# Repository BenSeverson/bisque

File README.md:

<p align="center">
  <picture>
    <source media="(prefers-color-scheme: dark)" srcset="docs/logo-banner-dark.svg" />
    
  </picture>
</p>

<p align="center">

</p>

<p align="center">
  <a href="https://benseverson.github.io/bisque/"><b>▶ Try the live web UI demo</b></a> — interactive, no hardware required
</p>

## Features

**Temperature Control**
- PID controller with auto-tuning (Ziegler-Nichols relay method)
- 1-second control loop with time-proportional SSR output
- Thermocouple calibration offset

**Firing Profiles**
- Up to 20 custom profiles with 16 segments each (ramp rate, target temp, hold time)
- Orton cone firing (cones 022-13) with slow, medium, and fast heating speeds
- Delayed start

**Safety**
- Over-temperature protection (hardware max 1400 C, user-configurable limit)
- Thermocouple fault detection (open circuit, short to GND/VCC)
- Rate-of-rise monitoring (detects runaway >2x programmed rate)
- Not-rising detection (alerts if <10 C rise in 15 min)
- Emergency stop with immediate SSR cutoff

**Web Dashboard**
- Real-time temperature chart with profile overlay (React + Recharts)
- Profile builder with cone fire mode
- Firing history with CSV trace export and cost estimation
- Settings: calibration, safety limits, webhooks, API token

**iOS App**
- Full remote control (SwiftUI)
- Finds the kiln on your Wi-Fi automatically (Bonjour), no IP address to type
- Dynamic Island live activities during firing
- Local notifications for firing complete/error

**LCD Display**
- 4.0" TFT (480x320) with LVGL, adaptive single-screen dashboard (idle/active/paused/complete/error)
- 5-way nav switch (up/down/select/left/right), SELECT-driven modals for profile pick and firing control

**Connectivity**
- Wi-Fi with mDNS (`bisque.local`)
- REST API with optional bearer token auth
- WebSocket for real-time streaming
- Webhook notifications (firing complete/error)

## Screenshots

**Web Dashboard** (React)

**LCD Display** (LVGL on 4.0" TFT)

**iOS App** (SwiftUI)

## Hardware

The controller is a single board in [`hardware/kicad/`](hardware/kicad/) — a full KiCad project (schematic + routed **4-layer** board, 100 × 100 mm). Its GPIO map is [`docs/pin-assignments.md`](docs/pin-assignments.md).

It integrates the ESP32-S3-WROOM-1U module (external U.FL antenna), two MAX31856 thermocouple front-ends, two SSR drive channels behind a hardware watchdog, a current-transformer input read by the ESP32's ADC, a ULN2003 auxiliary output bank, three protected dry-contact inputs, USB-C flashing, and an alarm buzzer — with screw terminals for the field wiring and keyed connectors for the display and nav-switch looms. Gerbers, drill files, and an assembly BOM/CPL are committed and ready to upload to a board house.

See [`hardware/kicad/README.md`](hardware/kicad/README.md) for the full BOM, fabrication notes, and the regeneration workflow. GPIO assignments mirror the firmware's `Kconfig` defaults, so stock firmware runs unmodified.

[`hardware/enclosure/`](hardware/enclosure/README.md) documents a complete enclosure build around an off-the-shelf wall-mount steel box — layout, SSR thermal sizing, mains/SELV segregation, and a printable 1:1 drill template for the door.

> **Safety warning:** Kilns operate at dangerous temperatures and voltages. Ensure all high-voltage wiring is performed by a qualified electrician. Use appropriate safety equipment and never leave a firing kiln unattended.

## Getting Started

### Prerequisites

- [ESP-IDF v6.1.1](https://docs.espressif.com/projects/esp-idf/en/v6.1.1/esp32s3/get-started/)
- Node.js 18+
- [XcodeGen](https://github.com/yonaskolb/XcodeGen) (for iOS development)

### Dev Container (recommended)

The fastest way to a reproducible toolchain is the VS Code dev container — it
pins the exact ESP-IDF v6.1.1 image CI uses plus Node 24, the static-analysis
tools, and the Claude Code CLI. Open the repo in VS Code and run **Dev
Containers: Reopen in Container**. Everything below (firmware build, web UI,
`make ci`) then works in the container terminal; only flashing needs a bench.
See [docs/devcontainer.md](docs/devcontainer.md).

### Firmware

```bash
# Build web UI assets first
cd web_ui && npm install && npm run build && cd ..

# Gzip assets for SPIFFS
gzip -k -9 spiffs_data/www/assets/*.js spiffs_data/www/assets/*.css

# Build and flash firmware
source ~/.espressif/v6.1.1/esp-idf/export.sh
idf.py build
idf.py flash monitor
```

### Web UI Development

```bash
cd web_ui
npm install
npm run dev    # Starts dev server with mock kiln simulator
```

### iOS App

```bash
# Generate Xcode project
cd ios/Bisque
xcodegen generate
open Bisque.xcodeproj
```

For simulator testing, start the mock server first:

```bash
cd web_ui && npm run mock-server   # HTTP + WebSocket on localhost:8080
```

In the iOS simulator, tap "Use Mock Server" on the connection screen.

<details>
<summary><strong>Simulator / Mock Server</strong></summary>

A mock kiln server simulates the full API (status, profiles, firing, settings, history, autotune, diagnostics) with realistic temperature physics so you can develop and test without hardware.

### Web UI development

The mock server runs automatically as a Vite plugin when you start the web UI dev server:

```bash
cd web_ui
npm run dev
```

The mock is enabled by default. To disable it and proxy to a real kiln instead:

```bash
VITE_MOCK=false npm run dev
```

Control simulation speed with `VITE_MOCK_SPEED` (default `60` = 60x real-time):

```bash
VITE_MOCK_SPEED=120 npm run dev
```

### iOS app development

A standalone mock server is available for testing the iOS app in the Xcode simulator:

```bash
cd web_ui
npm run mock-server
```

This starts an HTTP + WebSocket server on `localhost:8080`. To change the port or simulation speed:

```bash
MOCK_PORT=9000 MOCK_SPEED=120 npm run mock-server
```

### LCD Simulator

A standalone SDL2-based simulator renders the LVGL display UI on your desktop:

```bash
cd simulator
cmake -B build && cmake --build build
./build/bisque_sim
```

Requires SDL2 (`brew install sdl2` on macOS).

</details>

## Architecture

```
main/                 App entry point, FreeRTOS task creation
components/
  app_config/         Pin definitions, hardware constants
  thermocouple/       MAX31856 SPI driver (2 channels)
  pid_control/        PID controller + Ziegler-Nichols auto-tune
  firing_engine/      Multi-segment firing state machine
  safety/             Watchdog, over-temp, fault detection
  cone_table/         Orton cone temperature lookup (022-13)
  history/            Firing history + temperature traces (NVS)
  display/            ST7796S LCD + LVGL UI (adaptive dashboard)
  web_server/         REST API + WebSocket server
  wifi_manager/       Wi-Fi STA/AP + mDNS
web_ui/               React/TypeScript web dashboard
ios/Bisque/           SwiftUI iOS app
simulator/            LVGL SDL2 desktop simulator
tests/host/           Pure-logic + accelerated firing unit tests (CMake/Unity)
docs/                 Wiring diagrams, screenshots, bench smoke test
```

## Testing

CI runs five automated test layers on every PR — pure-logic unit tests
and accelerated firing scenarios (`tests/host/`), a UI screenshot
regression suite (`simulator/ --diff`), web UI unit tests, and a
cross-language API contract test that validates firmware JSON output
against the frontend's zod schemas.

Before tagging a release, run the [bench smoke test](docs/bench-smoke-test.md) — a 3-8 minute hardware
run that verifies the parts CI can't touch: real SSR clicks, real
thermocouple readings, history persistence across reboot.

## Network security

**Bisque assumes the network it sits on is trusted.** It is a LAN-only
device: the HTTP API and the WebSocket telemetry feed are plain `http://`
and `ws://`, with no TLS. Anyone who can see traffic on the same Wi-Fi can
read the API token and every command sent with it.

The optional API token (Settings → API Token) is therefore a lock on the
front door, not protection against a hostile network. It stops a
housemate's laptop or a curious guest from starting a firing; it does not
stop someone who is already capturing your Wi-Fi traffic. Concretely:

- The token is sent as an `Authorization: Bearer` header on every REST
  request and compared in constant time on the device.
- The WebSocket telemetry feed (`/api/v1/ws`) is authenticated by the same
  check as the REST API. Browsers cannot set headers on a WebSocket
  handshake, so the web UI presents the token as a `?token=` query
  parameter instead — which means that on this one route the credential does
  reach anywhere the URL does, including proxy logs and browser history. The
  iOS app uses `URLSession`, which can set the header, and does. Dropping the
  query parameter would lock every browser out of live telemetry, so it is a
  deliberate trade rather than an oversight.
- Firmware updates are fetched over HTTPS with certificate validation
  against the bundled root store, and the downloaded image is checked
  against the SHA-256 in the release manifest. So an OTA is not exposed by
  the local network being readable — its trust rests on GitHub's TLS, not on
  your LAN.

If that trust assumption does not hold for your network, put the kiln on an
isolated VLAN or guest SSID rather than relying on the token. TLS on-device
with certificate pinning in the clients has been considered and is tracked
in [#149](https://github.com/BenSeverson/bisque/issues/149); it is a
significant amount of firmware and app complexity for a home LAN, and has
not been implemented.

**Never expose a kiln controller directly to the internet.** No port
forwarding, no DMZ. This is a device that applies mains power to a heating
element in an unattended room.

## Releases

Firmware is distributed as [GitHub Releases](https://github.com/BenSeverson/bisque/releases),
each with a full ESP32-S3 flash kit and Sigstore build-provenance
attestations. See [RELEASING.md](RELEASING.md) for the versioning scheme and
the procedure for cutting a release.

## License

[MIT](LICENSE)

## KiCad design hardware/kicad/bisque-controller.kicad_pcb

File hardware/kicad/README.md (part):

# Bisque Kiln Controller — KiCad PCB

The controller board. This is **rev B**, a respin of the original prototype
rather than a variant — it replaced the thermocouple front-end with an
incompatible part, added a second SSR zone and a digital current-sense chip,
moved most GPIOs, and swapped the module variant.
4-layer, 100 × 100 mm, built for **JLCPCB assembly**: 0805 passives,
QFN/TSSOP/SOIC/SOT ICs, SMD tact switches and the ESP32-S3-WROOM-1U module's
castellated pads all go down the SMT line, and JLCPCB hand-solders the fourteen
through-hole parts (terminals, wafers, buzzer) on the same order — see
"Fabrication & assembly" below for why that is cheaper than fitting them
yourself. The design record for
this respin, including the routing escalation that forced the layer count,
is `docs/superpowers/specs/2026-08-10-pcb-rev-b-hardware-design.md`; the
fab-readiness sign-off is `FAB-READINESS-REVIEW-REVB.md`.

**Rev C (2026-11-26)** is the current revision. It removes two blocks from
B.5 and changes the pin map for the first time since rev B: the WS2812 status
LED is gone (its indications live on the LCD and the web UI), and the ADE7953
metering chip, its oscillator and the second CT terminal are replaced by one
current-transformer input read by the ESP32's own ADC. 31 parts out, 6 in, 167
placed, 49 BOM lines. The reasoning is the rev C section of `DESIGN-NOTES.md`.
Much of this README is a record of how the board got here, so U7, Y1, LED1 and
J17 still appear below wherever the story involves them; the sections that
describe the board as it is (features, bill of materials, fabrication) are
current.

Built and validated with **real KiCad** (10.0.5, pcbnew Python API +
kicad-cli): footprints come from KiCad's installed libraries, ground/power
plane pours are filled and checked by `kicad-cli pcb drc --refill-zones` —
**zero errors, zero unconnected, zero warnings**
(`bisque-controller-drc.rpt`) — and the schematic passes a netlist round-trip
check (KiCad's exported netlist diffed against the design's connectivity
table — 92 nets, 0 mismatches). The 3D renders in `3d/` are raytraced by
`kicad-cli pcb render` with the official component models.

| File | What it is |
|---|---|
| `bisque-controller.kicad_pro` | Project. Hand-maintained **except** two blocks, both derived and both written *after* the board is saved because `pcbnew.SaveBoard()` blanks them: `schematic.top_level_sheets` (`project_sync.py::sync_project()`) and `net_settings` (`gen_pcb.py::sync_netclasses()`, from `ROUTE_ORDER`) — see below |
| `bisque-controller.kicad_sch` | Root of the hierarchical schematic: a sheet symbol per functional area (`sheets/power`, `mcu`, `kiln`, `io`, `ct`) plus the notes block and the mechanical parts (mounting holes H1–H4, fiducials FID1–FID3), wired as a block diagram: each sheet symbol carries a pin per net that crosses sheets. Within a sheet: one hierarchical label per crossing net, local labels for everything else, real power ports for rails; no global labels. Hand-owned; `make pcb-netlist` exports its connectivity. |
| `bisque-controller.kicad_pcb` | Board: placed, fully routed, 4 layers (F.Cu/B.Cu signals, In1.Cu GND plane, In2.Cu +3V3 plane), on JLCPCB's `JLC04161H-7628` 1.6 mm stack-up — see "The physical stack-up" |
| `bisque-controller.kicad_dru` | JLCPCB's standard 4-layer process as KiCad custom rules — **not generated**, and not a statement of design intent: every limit in it is JLC's *absolute minimum*, so a violation means something slipped off the design's own floor (0.3 mm track, 0.2 mm clearance, 0.6/0.3 vias, all from `net_settings`) far enough to hit the fab's. KiCad reads it by project name, so it survives regeneration untouched and the existing `kicad-cli pcb drc` pass picks it up for free — see "Fabrication & assembly at JLCPCB" |
| `3d/board-3d-*.png` | Raytraced renders, kicad-cli — straight orthographic **top** and **bottom** only. The angled iso/front views were dropped: they look better than they read, and these images get used to check placement and silk, not to advertise |
| `bisque-controller-drc.rpt` | KiCad DRC report, now including the `.kicad_dru` rules above (0 errors, 0 unconnected, 0 warnings — the 109 silkscreen warnings went with the silk packer, see "Regenerating the files") |
| `gerbers/` | Fabrication outputs (kicad-cli: F.Cu, B.Cu, **In1.Cu, In2.Cu**, paste/silk/mask, Edge.Cuts, Excellon drill + job file) |
| `pdf/` | Schematic and board PDFs (kicad-cli) |
| `jlcpcb/` | The complete JLCPCB upload: `gerbers.zip` for fabrication, BOM + CPL for assembly, plus the shopping list for the parts you could hand-solder instead, and `mouser-order.csv` for the mating connectors |
| `generator/` | Scripts that build everything from one connectivity table |

## Opening it

Open `bisque-controller.kicad_pro` in KiCad 10 or newer (the board file
format and pcbnew API this generator uses require it — see "Regenerating the
files"). Zones ship **filled** (KiCad's own filler) and the board already
passes KiCad DRC; re-run it after any edit. The schematic embeds its
symbols; the board references the standard KiCad footprint libraries (and
was generated from them), plus the four vendored models in `3dmodels/`.

**Opening the project used to dirty it.** KiCad records the root sheet under
`schematic.top_level_sheets` in the `.kicad_pro` and writes that block itself
the first time anything touches the project — and what it writes depends on
who wrote it. The GUI knows the schematic's real root uuid; `kicad-cli pcb`
fills all-zeros, because the PCB tooling never loads a schematic and has no
uuid to record. So the file grew an unexplained diff after a regen and could
flip between two values depending on which tool ran last.

`project_sync.py::sync_project()` (used by `sync_board.py`) now derives the entry from the same `ROOT`
constant the schematic's own `(uuid ...)` comes from, and runs on every
`pcb-sync`. Whoever opens the project next finds it already
correct and leaves it alone — kicad-cli only ever *adds* the block when it is
missing and preserves a populated one, which is what makes deriving it
sufficient rather than a tug-of-war. The rewrite is a whole-file json
round-trip, safe because KiCad emits plain 2-space-indented JSON that
re-dumps byte for byte; do not replace it with a hand-rolled text patch.

## What's on the board

- **U1 — ESP32-S3-WROOM-1U-N16R2** module (16 MB flash / 2 MB **quad**
  PSRAM — matches `sdkconfig.defaults`' `CONFIG_SPIRAM_MODE_QUAD` + the
  16 MB OTA partition table), at the top edge. The **1U** variant carries a
  **U.FL connector for an external antenna** rather than the standard
  WROOM-1's on-package PCB antenna: a kiln controller mounts on or near a
  large grounded steel enclosure, which makes a PCB antenna close to
  non-functional, and the 1U's antenna can be placed on a pigtail somewhere
  that actually radiates. It also reclaims the ~330 mm² antenna keep-out
  band the WROOM-1 footprint would require — freed for parts and ground
  pour on a board that turned out to need every square millimeter (see
  "Density and the 4-layer stack-up" below). **The U.FL pigtail (U.FL → SMA
  bulkhead) and the 2.4 GHz antenna are accessories, not BOM lines** — buy
  them separately (see the hand-solder/shopping-list note below) and drill
  an SMA bulkhead hole in the enclosure. U.FL is rated for ~30 mating
  cycles, so treat the connection as assemble-once, not a field-serviceable
  connector.

  **Certification caveat.** Espressif's modular certification for the
  WROOM-1U is granted against specific antenna types and gains. Fitting a
  non-approved (e.g. high-gain) antenna steps outside that approval — see
  `CERT-001` in `FAB-READINESS-REVIEW-REVB.md`. Use an antenna within the
  certified list unless you're prepared to re-certify.

- **Power**: 24 V DC in on screw terminal **J2** (top-left) *or* USB-C.
  The 24 V side runs J2 → F1 (750 mA/33 V resettable fuse) → D8 (SMAJ30A TVS)
  → **Q8** (AO3401A P-FET, reverse polarity) → **U11**, an XL1509-5.0 buck in
  the south-east corner that makes `BUCK_5V`; **U12** (TPS2116) then selects
  between `BUCK_5V` and USB VBUS to make `+5V`, and a **TLV1117LV33**
  (U2, SOT-223) drops that to 3V3.
  Regulating rather than dropping is the point: +5V used to be literally the
  input minus a Schottky, so every diode drop and every turn of the
  installer's trim pot landed on the SSR drive and the relay coil at once. Both of the board's remaining series diodes are now
  gone with it — the reverse-polarity SS34 is Q8 (~39 mV instead of ~0.4 V,
  which matters because `VIN_P` feeds both 24 V SSR terminals as well as the
  buck) and the USB ORing SS34 is U12 (~40 mΩ).

  **U12 runs in priority mode, not highest-voltage-wins, and that is the
  whole reason it is a mux and not an ideal diode.** A 5.25 V USB host is
  higher than a 5.0 V buck, so a plain ORing part would let a laptop source
  the relay bank and both SSR terminals; the diode used to prevent that for
  free by dropping. MODE ties to VIN1 and R63/R64 divide `BUCK_5V` into PR1
  with a 4.0 V threshold, so the buck wins whenever it is up. U12 also
  blocks USB back-feeding the unpowered buck, which closes fab-review
  finding **C1** (5 V on U11's FB and switch pins during every USB-only
  flashing session). Its ST pin is left unconnected on purpose — see
  `DESIGN-NOTES.md` at U12 for why that GPIO is not worth the route.

  `BUCK_5V` and `+5V` are deliberately separate nets: C44/**C46** are the
  buck's compensation (C46 is the electrolytic supplying the ESR zero — since
  2026-10-28 a Panasonic FK with its 0.36 Ω *specified* at 100 kHz, beside one
  22 µF ceramic rather than two; `DESIGN-NOTES.md` at C46 and C44) and
  belong on the buck's side of the mux, not the load's. The input pair C41/C42
  is chosen on Samsung's bias curve: 1210 X7R 4.7 µF holding 3.1 µF each at
  24 V, where the 1206 10 µF they replace held 1.35 µF. The 5 V rail is rated
  1.0 A at 50 °C in-box ambient (`DESIGN-NOTES.md` at C41, "LOAD BUDGET");
  the regulator's 2 A headline is not a rating of this board.
  Power LED (green) on 3V3. The display (below) draws from +5V directly, not
  through U2 — its backlight and panel logic were the dominant unmodeled load
  on the LDO, and moving them off keeps U2's junction temperature comfortably
  under its 125°C limit even at a hot enclosure ambient. The +3V3 rail also
  now lives on its own **inner plane** (In2.Cu) rather than a surface pour —
  see the stack-up note below.
- **Thermocouples ×2**: **MAX31856MUD+** (U3 channel 1 / U5 channel 2,
  TSSOP-14), K-type on screw terminals **J3** (channel 1) / **J8** (channel
  2), each with its datasheet-specified differential + common-mode input
  filter, sharing the SPI bus (MISO + its own CS: `TC1_CS` / `TC2_CS`). This
  replaces rev A's single MAX31855KASA+ entirely — the two parts are not
  pin-compatible, and no attempt was made to support both on one board.

  **Ungrounded-junction thermocouple probes are required.** Both MAX31856s
  reference their T− input to board ground. Two grounded-junction probes
  sharing one kiln chamber would form a ground loop through the kiln body
  itself; use ungrounded-junction (isolated-tip) K-type probes on both
  channels. This is a documentation obligation, not something the board
  enforces electrically.
- **SSR drive ×2, 24 V opto-driven high-side P-FET, ground-referenced (rev
  B.4)**: screw terminals **J4** (zone 1) / **J9** (zone 2), each
  **pin 1 = the switched +** (`SSR1_OUT` / `SSR2_OUT`, silk `OUT`) and
  **pin 2 = board `GND`**. Per channel: GPIO → 220 Ω → the LED of a TLP291
  (**U8** zone 1, **U9** zone 2) → GND; the opto's transistor pulls the gate
  of an **LP2309LT1G** (**Q5** / **Q6**, 60 V P-channel) down through
  **10 kΩ** (R69/R70), an **8.2 V zener** (D13/D14) gate-to-source sets the
  drive from the rail, and **10 kΩ** (R7/R20) gate-to-source holds it off.
  Both sources hang off **`SSR_24V`**, which is `VIN_P` through **Q9**, a
  third LP2309LT1G that is the watchdog's cutoff (see below). A green
  indicator LED (LED3/LED4, amber before the 2026-11-07 BOM-line merge) + 10 kΩ sits across each terminal pair, so it lights only
  when the channel is actually conducting. **D9**/**D10** freewheel each
  terminal for inductive loads. The board supplies the SSR control loop.
  (The SSRs themselves and all mains wiring stay outside this board.)
  Because the `−` pin is ground, an SSR lead that chafes onto the earthed
  enclosure is the wiring diagram, not a fault — the 2026-10-05 review's
  item 3, which B.2's switched-return topology could not cover. Rev B.2/B.3
  boards had pin 1 always live (silk `24V`) and switched the return; the
  pin order is unchanged, so a loom built to that silk still lands right.

  **Current budget, and it is a limit rather than a note.** The two channels
  share what is left of F1's *derated* hold current after the buck: **280 mA
  at the board's 50 °C in-box rating, 180 mA at 60 °C** (derived at F1 in
  `DESIGN-NOTES.md`, 2026-10-29, from the PPTC's derating table, the
  HDR-15-24's own derating and U11 at its 1.0 A ceiling). Two SSR inputs
  plus their indicators is ~40 mA and fits at any ambient. One 24 V coil
  beside an SSR: ≤ 260 mA (6.2 W) at 50 °C, ≤ 160 mA at 60 °C — a 5.4 W
  TeSys-D-class coil fits at 50 °C and not at 60. Two coils: ≤ 140 mA each
  at 50 °C, ≤ 90 mA each at 60 °C. The "~400 mA" quoted before was the 25 °C
  figure. F1 is not enlarged to buy more: under the in-box supply the
  supply's 0.63 A is the next limit anyway, and a 1.1 A PPTC's 2.2 A trip
  would put the clamped fault rail at 39.9 V against U11's 40 V.

  **The optocouplers are containment, not isolation, and that distinction is
  load-bearing.** Rev B opto-*isolated* both channels — dry-contact terminals,
  a four-layer pour keepout across the opto row, `SJ3`/`SJ4` to tie each
  collector to board +5 V, and `check_isolation.py` — and that was **reversed**
  before fab, because an optocoupler only isolates if the SSR control loop is
  powered from a supply that is *not this board*, and this board's is.
  **That reasoning still stands and is not being overturned.** These terminals
  are still board-powered, both sides still share `GND`, and there is still no
  pour keepout, no router keepout, no rule area and no `check_isolation.py`.
  Do not re-add any of them; read commit `93a31d7` first.

  What changed is the failure the parts are bought for. At 5 V, a channel
  MOSFET failing gate-to-drain put 5 V through 100 Ω into a GPIO and the
  ESP32's clamp survived it. At 24 V the same single failure puts ~240 mA into
  that clamp and takes the module with it. The opto removes the conductor: the
  only thing the MCU touches is an LED. It is also not more parts than the
  alternative — a gate-to-GND zener contains the same fault for the same one
  part per channel, but contains it *by conducting*, so it has to survive the
  fault to work and fails open silently.

  **The opto is a TLP291 in SOP-4, not the LTV-817S this started as, and the
  reason is geometry.** The SMD-DIP4 body is 12.04 mm across its courtyard;
  the corridor between `J4`/`J9` and the rest of the block is ~5.5 mm and has
  to carry both these parts and the four per-terminal legends (`OUT`/`GND`,
  each locked to its own screw's y and free only in x). A 12 mm opto leaves
  those legends nowhere to go, and they print on the terminal body — three
  `check_silk` failures that no amount of re-spacing fixes, because the
  corridor is simply too narrow. At 8.50 × 3.10 mm it opens to ~6.7 mm.
  It costs one Extended feeder where the LTV-817S was Basic, and buys 80 V
  `V_CEO` against 35 V, which is free margin on a 24 V board.

  The 220 Ω is sized against the ESP32's **guaranteed** `V_OH`
  (0.8 × VDD = 2.64 V), not against 3.3 V: the opto's CTR bin is only
  specified at `I_F` = 5 mA and falls off steeply below it, and 330 Ω at that
  corner gives 4.7 mA. 220 Ω gives 7.0 mA there, 5.6 mA with `V_F` also at
  its maximum, and 10.0 mA typical — half the ESP32's recommended source
  current.

  The gate drive comes from a **zener, not from the opto's CTR**, and that is
  deliberate: with the opto saturated the R69/R7 pair alone would put half
  the rail across the gate (11.9 V at 24 V, 18.8 V in a clamped 38 V fault,
  24 V on the 48 V transient), so D13/D14 clamp `V_SG` to 8.2 V from
  ~17 V upwards — the whole 21.6–29 V trim range and the fault alike. The
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
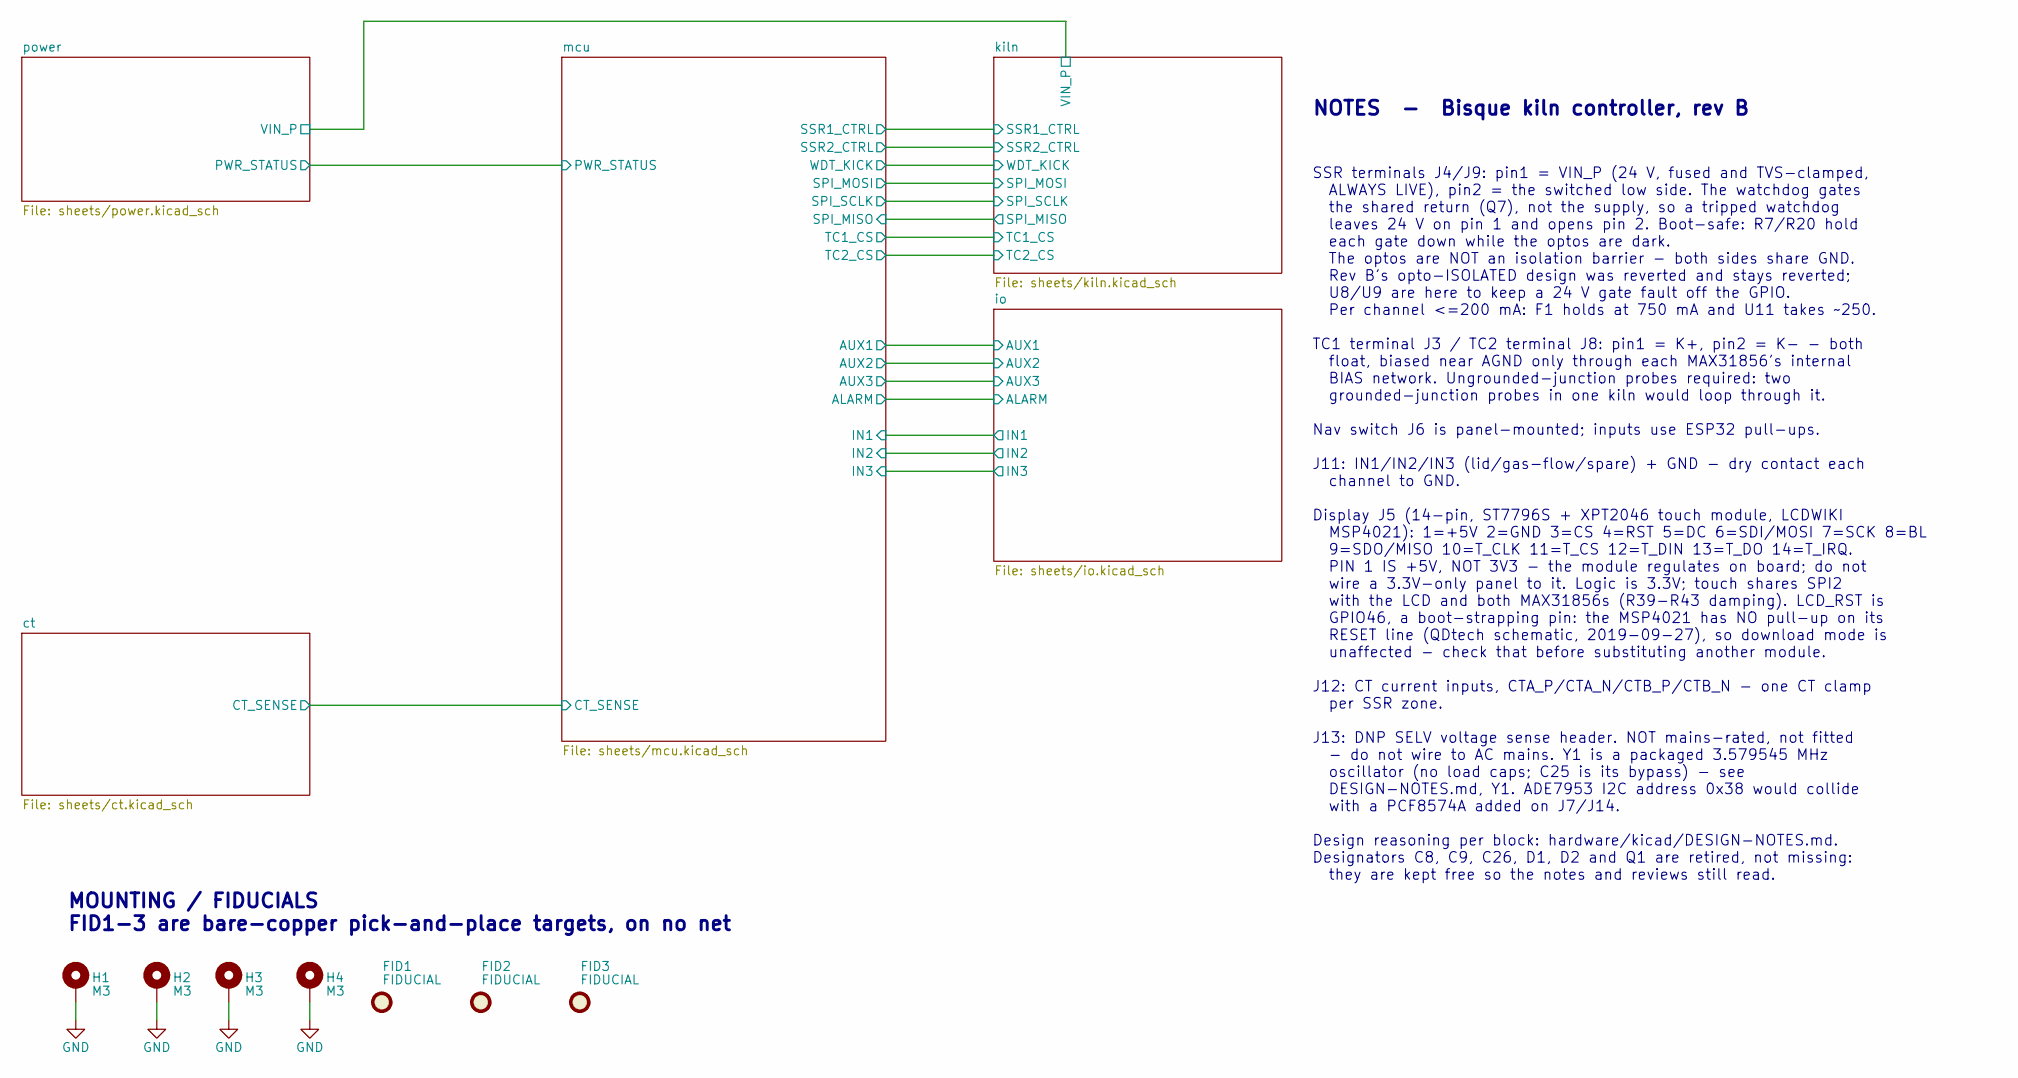
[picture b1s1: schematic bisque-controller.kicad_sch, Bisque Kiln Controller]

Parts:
FID1, FID2, FID3: FIDUCIAL; Fiducial_1mm_Mask2mm
H1, H2, H3, H4: M3; MountingHole_3.2mm_M3_Pad_Via

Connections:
GND: H1.1, H2.1, H3.1, H4.1; also elsewhere on the board

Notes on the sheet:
NOTES - Bisque kiln controller, rev B
SSR terminals J4/J9: pin1 = VIN_P (24 V, fused and TVS-clamped, ALWAYS LIVE), pin2 = the switched low side. The watchdog gates the shared return (Q7), not the supply, so a tripped watchdog leaves 24 V on pin 1 and opens pin 2. Boot-safe: R7/R20 hold each gate down while the optos are dark. The opto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
MOUNTING / FIDUCIALS FID1-3 are bare-copper pick-and-place targets, on no net

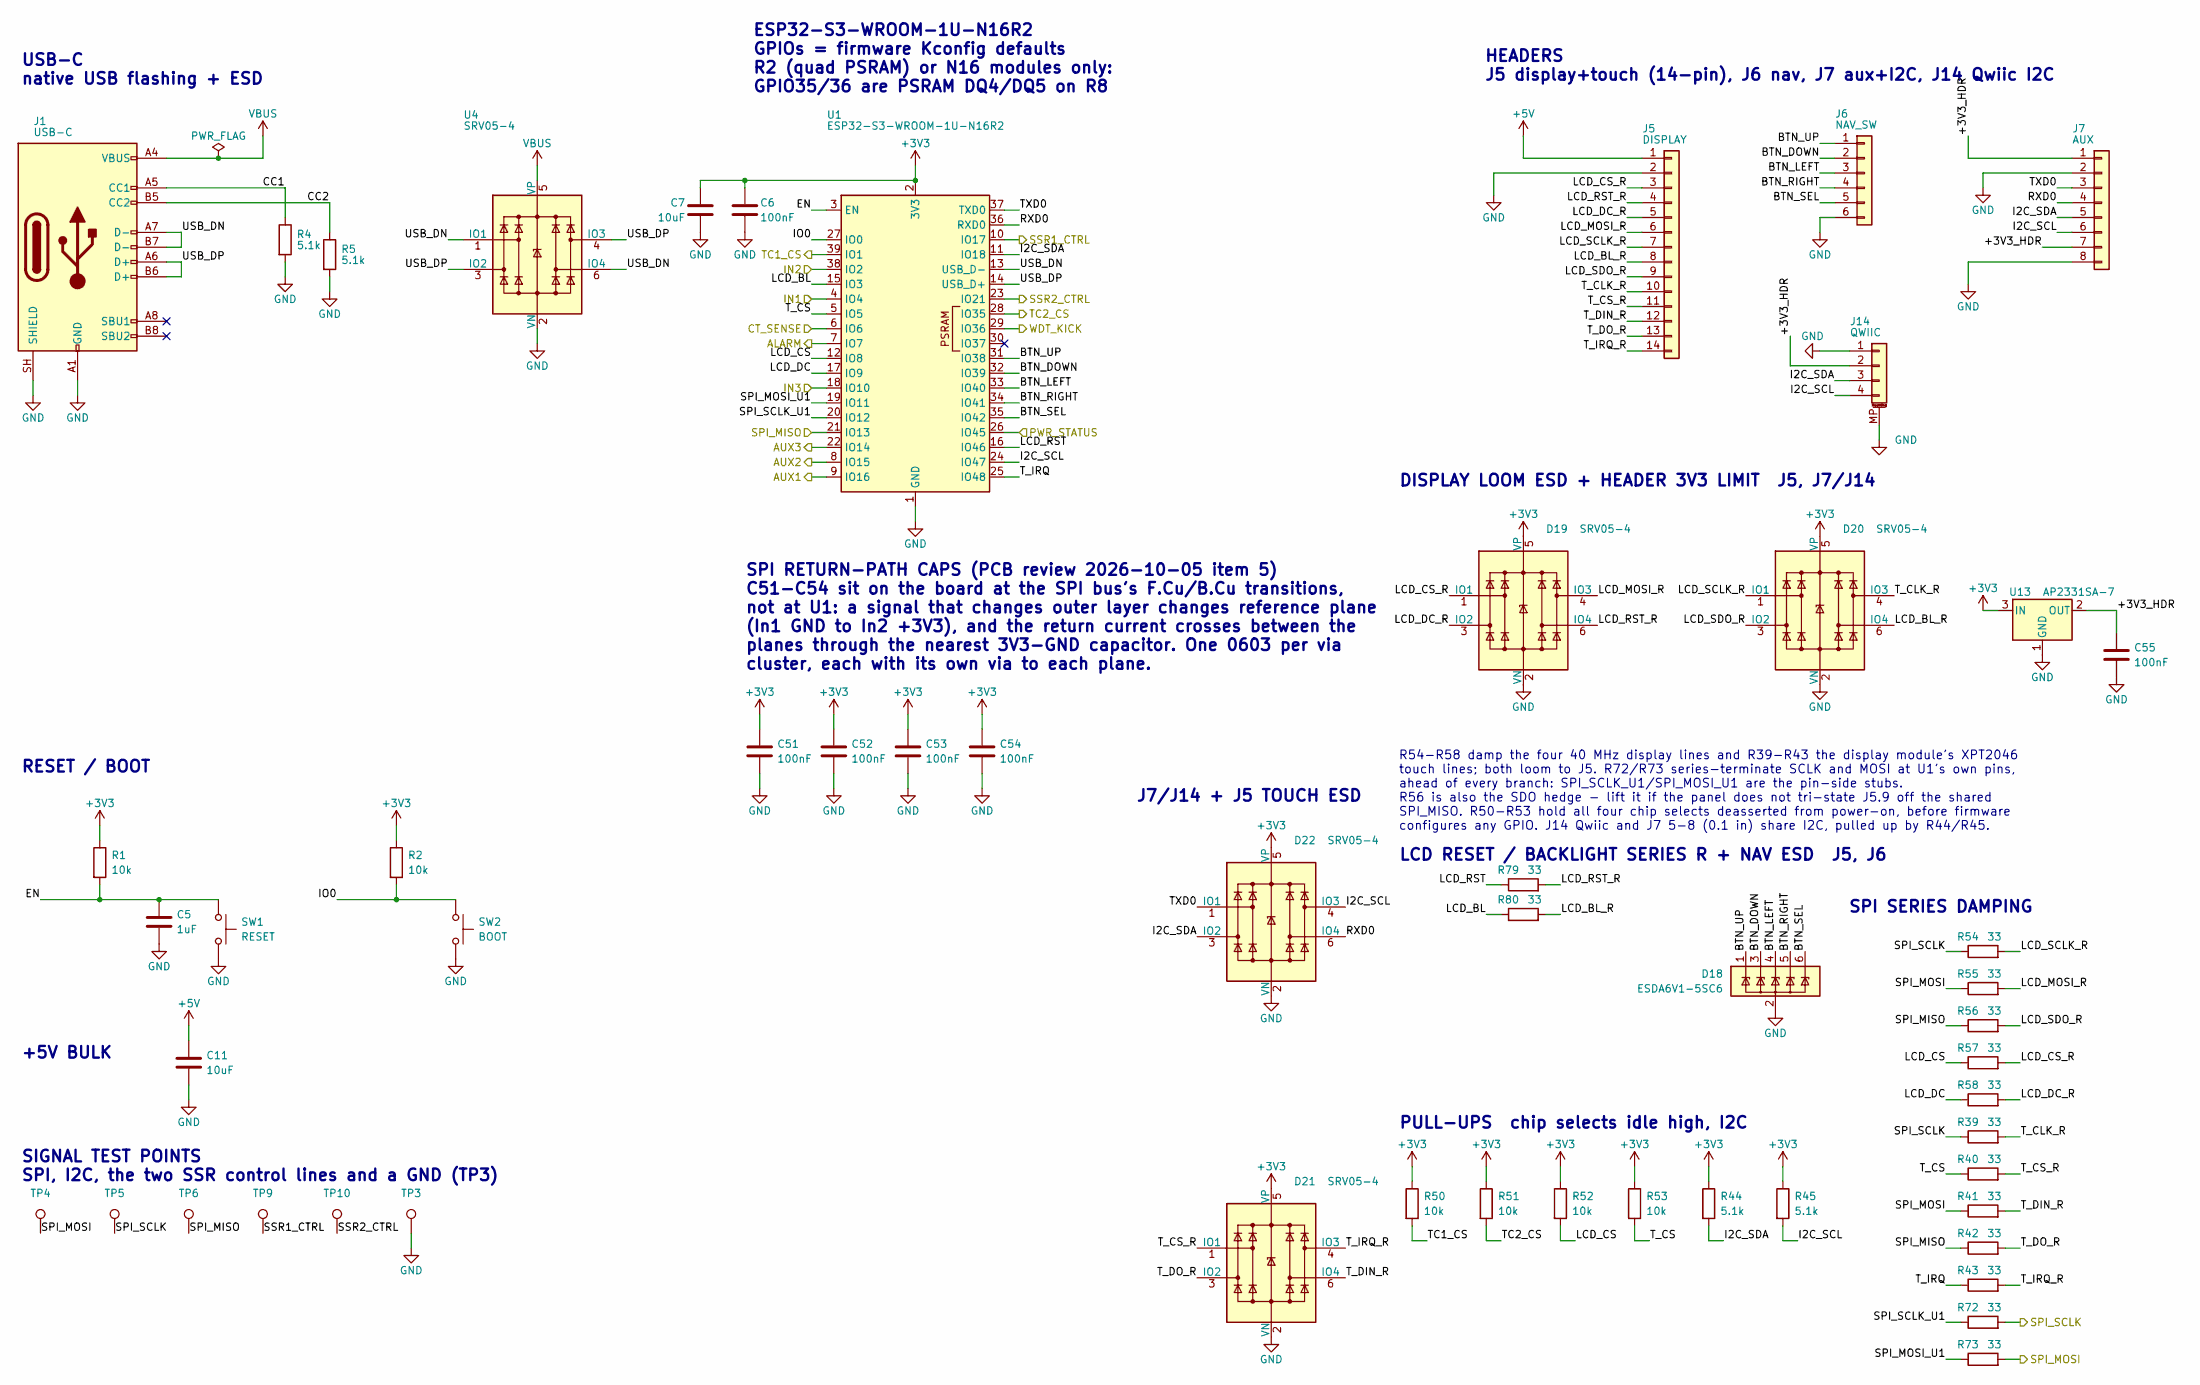
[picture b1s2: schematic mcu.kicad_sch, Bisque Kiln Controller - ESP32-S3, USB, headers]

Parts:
C5: 1uF; C_0805_2012Metric; MPN CL21B105KBFNNNE; LCSC C28323
C6, C51, C52, C53, C54, C55: 100nF; C_0603_1608Metric; MPN CC0603KRX7R9BB104; LCSC C14663
C7, C11: 10uF; C_0805_2012Metric; MPN CL21A106KAYNNNE; LCSC C15850
D18: ESDA6V1-5SC6; SOT-23-6; MPN ESDA6V1-5SC6; LCSC C2827672
D19, D20, D21, D22: SRV05-4; SOT-23-6; MPN SRV05-4; LCSC C7420376
J1: USB-C; USB_C_Receptacle_HRO_TYPE-C-31-M-12; MPN TYPE-C-31-M-12; LCSC C165948
J5: DISPLAY; Molex_KK-254_AE-6410-14A_1x14_P2.54mm_Vertical; MPN XD-2510-14A; LCSC C17701004
J6: NAV_SW; Molex_KK-254_AE-6410-06A_1x06_P2.54mm_Vertical; MPN A2547WV-6P; LCSC C239381
J7: AUX; Molex_KK-254_AE-6410-08A_1x08_P2.54mm_Vertical; MPN 22272081; LCSC C240822
J14: QWIIC; JST_SH_SM04B-SRSS-TB_1x04-1MP_P1.00mm_Horizontal; MPN SM04B-SRSS-TB(LF)(SN); LCSC C160404
R1, R2, R50, R51, R52, R53: 10k; R_0805_2012Metric; MPN 0805W8F1002T5E; LCSC C17414
R4, R5, R44, R45: 5.1k; R_0805_2012Metric; MPN 0805W8F5101T5E; LCSC C27834
R39, R40, R41, R42, R43, R54, R55, R56, R57, R58, R72, R73, R79, R80: 33; R_0603_1608Metric; MPN 0603WAF330JT5E; LCSC C23140
SW1: RESET; SW_Push_1P1T_XKB_TS-1187A; MPN TS-1187A-B-A-B; LCSC C318884
SW2: BOOT; SW_Push_1P1T_XKB_TS-1187A; MPN TS-1187A-B-A-B; LCSC C318884
TP3: GND; TestPoint_Pad_D1.0mm
TP4: SPI_MOSI; TestPoint_Pad_D1.0mm
TP5: SPI_SCLK; TestPoint_Pad_D1.0mm
TP6: SPI_MISO; TestPoint_Pad_D1.0mm
TP9: SSR1_CTRL; TestPoint_Pad_D1.0mm
TP10: SSR2_CTRL; TestPoint_Pad_D1.0mm
U1: ESP32-S3-WROOM-1U-N16R2; ESP32-S3-WROOM-1U; MPN ESP32-S3-WROOM-1U-N16R2; LCSC C3013945
U4: SRV05-4; SOT-23-6; MPN SRV05-4; LCSC C7420376
U13: AP2331SA-7; SOT-23; MPN AP2331SA-7; LCSC C500764

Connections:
+3V3: C6.1, C7.1, C51.1, C52.1, C53.1, C54.1, D19.5 (VP), D20.5 (VP), D21.5 (VP), D22.5 (VP), R1.1, R2.1, R44.1, R45.1, R50.1, R51.1, R52.1, R53.1, U1.2 (3V3), U13.3 (IN); also elsewhere on the board
+3V3_HDR: C55.1, J7.1, J7.7, J14.2, U13.2 (OUT)
+5V: C11.1, J5.1; also elsewhere on the board
ALARM: U1.7 (IO7); also elsewhere on the board
AUX1: U1.9 (IO16); also elsewhere on the board
AUX2: U1.8 (IO15); also elsewhere on the board
AUX3: U1.22 (IO14); also elsewhere on the board
BTN_DOWN: D18.3 (IO2), J6.2, U1.32 (IO39)
BTN_LEFT: D18.4 (IO3), J6.3, U1.33 (IO40)
BTN_RIGHT: D18.5 (IO4), J6.4, U1.34 (IO41)
BTN_SEL: D18.6 (IO5), J6.5, U1.35 (IO42)
BTN_UP: D18.1 (IO1), J6.1, U1.31 (IO38)
CC1: J1.A5 (CC1), R4.1
CC2: J1.B5 (CC2), R5.1
CT_SENSE: U1.6 (IO6); also elsewhere on the board
EN: C5.1, R1.2, SW1.1, U1.3 (EN)
GND: C5.2, C6.2, C7.2, C11.2, C51.2, C52.2, C53.2, C54.2, C55.2, D18.2 (GND), D19.2 (VN), D20.2 (VN), D21.2 (VN), D22.2 (VN), J1.A1 (GND), J1.A12 (GND), J1.B1 (GND), J1.B12 (GND), J1.SH (SHIELD), J5.2, J6.6, J7.2, J7.8, J14.1, J14.MP (MountPin), R4.2, R5.2, SW1.2, SW2.2, TP3.1, U1.1 (GND), U1.40 (GND), U1.41 (GND), U4.2 (VN), U13.1 (GND); also elsewhere on the board
I2C_SCL: D22.4 (IO3), J7.6, J14.4, R45.2, U1.24 (IO47)
I2C_SDA: D22.3 (IO2), J7.5, J14.3, R44.2, U1.11 (IO18)
IN1: U1.4 (IO4); also elsewhere on the board
IN2: U1.38 (IO2); also elsewhere on the board
IN3: U1.18 (IO10); also elsewhere on the board
IO0: R2.2, SW2.1, U1.27 (IO0)
LCD_BL: R80.1, U1.15 (IO3)
LCD_BL_R: D20.6 (IO4), J5.8, R80.2
LCD_CS: R52.2, R57.1, U1.12 (IO8)
LCD_CS_R: D19.1 (IO1), J5.3, R57.2
LCD_DC: R58.1, U1.17 (IO9)
LCD_DC_R: D19.3 (IO2), J5.5, R58.2
LCD_MOSI_R: D19.4 (IO3), J5.6, R55.2
LCD_RST: R79.1, U1.16 (IO46)
LCD_RST_R: D19.6 (IO4), J5.4, R79.2
LCD_SCLK_R: D20.1 (IO1), J5.7, R54.2
LCD_SDO_R: D20.3 (IO2), J5.9, R56.2
PWR_STATUS: U1.26 (IO45); also elsewhere on the board
RXD0: D22.6 (IO4), J7.4, U1.36 (RXD0)
SPI_MISO: R42.1, R56.1, TP6.1, U1.21 (IO13); also elsewhere on the board
SPI_MOSI: R41.1, R55.1, R73.2, TP4.1; also elsewhere on the board
SPI_MOSI_U1: R73.1, U1.19 (IO11)
SPI_SCLK: R39.1, R54.1, R72.2, TP5.1; also elsewhere on the board
SPI_SCLK_U1: R72.1, U1.20 (IO12)
SSR1_CTRL: TP9.1, U1.10 (IO17); also elsewhere on the board
SSR2_CTRL: TP10.1, U1.23 (IO21); also elsewhere on the board
TC1_CS: R50.2, U1.39 (IO1); also elsewhere on the board
TC2_CS: R51.2, U1.28 (IO35); also elsewhere on the board
TXD0: D22.1 (IO1), J7.3, U1.37 (TXD0)
T_CLK_R: D20.4 (IO3), J5.10, R39.2
T_CS: R40.1, R53.2, U1.5 (IO5)
T_CS_R: D21.1 (IO1), J5.11, R40.2
T_DIN_R: D21.6 (IO4), J5.12, R41.2
T_DO_R: D21.3 (IO2), J5.13, R42.2
T_IRQ: R43.1, U1.25 (IO48)
T_IRQ_R: D21.4 (IO3), J5.14, R43.2
USB_DN: J1.A7 (D-), J1.B7 (D-), U1.13 (USB_D-), U4.1 (IO1), U4.6 (IO4)
USB_DP: J1.A6 (D+), J1.B6 (D+), U1.14 (USB_D+), U4.3 (IO2), U4.4 (IO3)
VBUS: J1.A4 (VBUS), J1.A9 (VBUS), J1.B4 (VBUS), J1.B9 (VBUS), U4.5 (VP); also elsewhere on the board
WDT_KICK: U1.29 (IO36); also elsewhere on the board

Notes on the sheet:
USB-C native USB flashing + ESD
SPI RETURN-PATH CAPS (PCB review 2026-10-05 item 5) C51-C54 sit on the board at the SPI bus's F.Cu/B.Cu transitions, not at U1: a signal that changes outer layer changes reference plane (In1 GND to In2 +3V3), and the return current crosses between the planes through the nearest 3V3-GND capacitor. O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
RESET / BOOT
+5V BULK
R54-R58 damp the four 40 MHz display lines and R39-R43 the display module's XPT2046 touch lines; both loom to J5. R72/R73 series-terminate SCLK and MOSI at U1's own pins, ahead of every branch: SPI_SCLK_U1/SPI_MOSI_U1 are the pin-side stubs. R56 is also the SDO hedge - lift it if the panel does not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
PULL-UPS chip selects idle high, I2C
DISPLAY LOOM ESD + HEADER 3V3 LIMIT J5, J7/J14
J7/J14 + J5 TOUCH ESD
LCD RESET / BACKLIGHT SERIES R + NAV ESD J5, J6
SPI SERIES DAMPING
HEADERS J5 display+touch (14-pin), J6 nav, J7 aux+I2C, J14 Qwiic I2C
SIGNAL TEST POINTS SPI, I2C, the two SSR control lines and a GND (TP3)
ESP32-S3-WROOM-1U-N16R2 GPIOs = firmware Kconfig defaults R2 (quad PSRAM) or N16 modules only: GPIO35/36 are PSRAM DQ4/DQ5 on R8

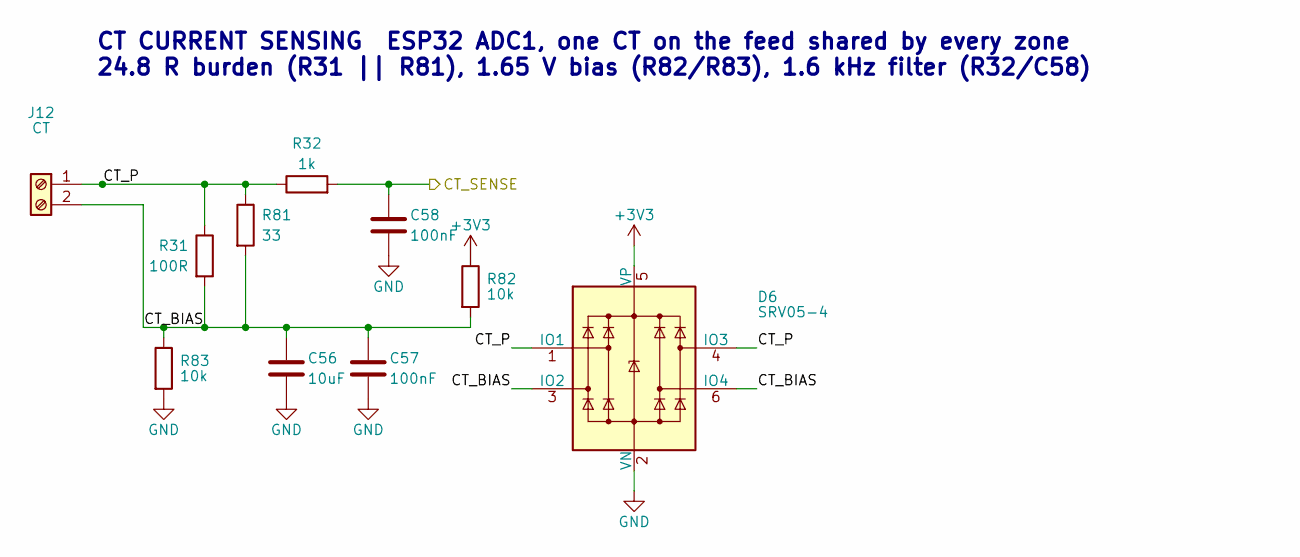
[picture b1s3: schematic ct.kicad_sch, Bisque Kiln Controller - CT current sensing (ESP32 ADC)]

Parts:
C56: 10uF; C_0805_2012Metric; MPN CL21A106KAYNNNE; LCSC C15850
C57, C58: 100nF; C_0603_1608Metric; MPN CC0603KRX7R9BB104; LCSC C14663
D6: SRV05-4; SOT-23-6; MPN SRV05-4; LCSC C7420376
J12: CT; TerminalBlock_Phoenix_MKDS-1,5-2-5.08_1x02_P5.08mm_Horizont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; MPN WJ500V-5.08-2P; LCSC C8465
R31: 100R; R_0805_2012Metric; MPN 0805W8F1000T5E; LCSC C17408
R32: 1k; R_0805_2012Metric; MPN 0805W8F1001T5E; LCSC C17513
R81: 33; R_0603_1608Metric; MPN 0603WAF330JT5E; LCSC C23140
R82, R83: 10k; R_0805_2012Metric; MPN 0805W8F1002T5E; LCSC C17414

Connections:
+3V3: D6.5 (VP), R82.1; also elsewhere on the board
CT_BIAS: C56.1, C57.1, D6.3 (IO2), D6.6 (IO4), J12.2, R31.2, R81.2, R82.2, R83.1
CT_P: D6.1 (IO1), D6.4 (IO3), J12.1, R31.1, R32.1, R81.1
CT_SENSE: C58.1, R32.2; also elsewhere on the board
GND: C56.2, C57.2, C58.2, D6.2 (VN), R83.2; also elsewhere on the board

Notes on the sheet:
CT CURRENT SENSING ESP32 ADC1, one CT on the feed shared by every zone 24.8 R burden (R31 || R81), 1.65 V bias (R82/R83), 1.6 kHz filter (R32/C58)

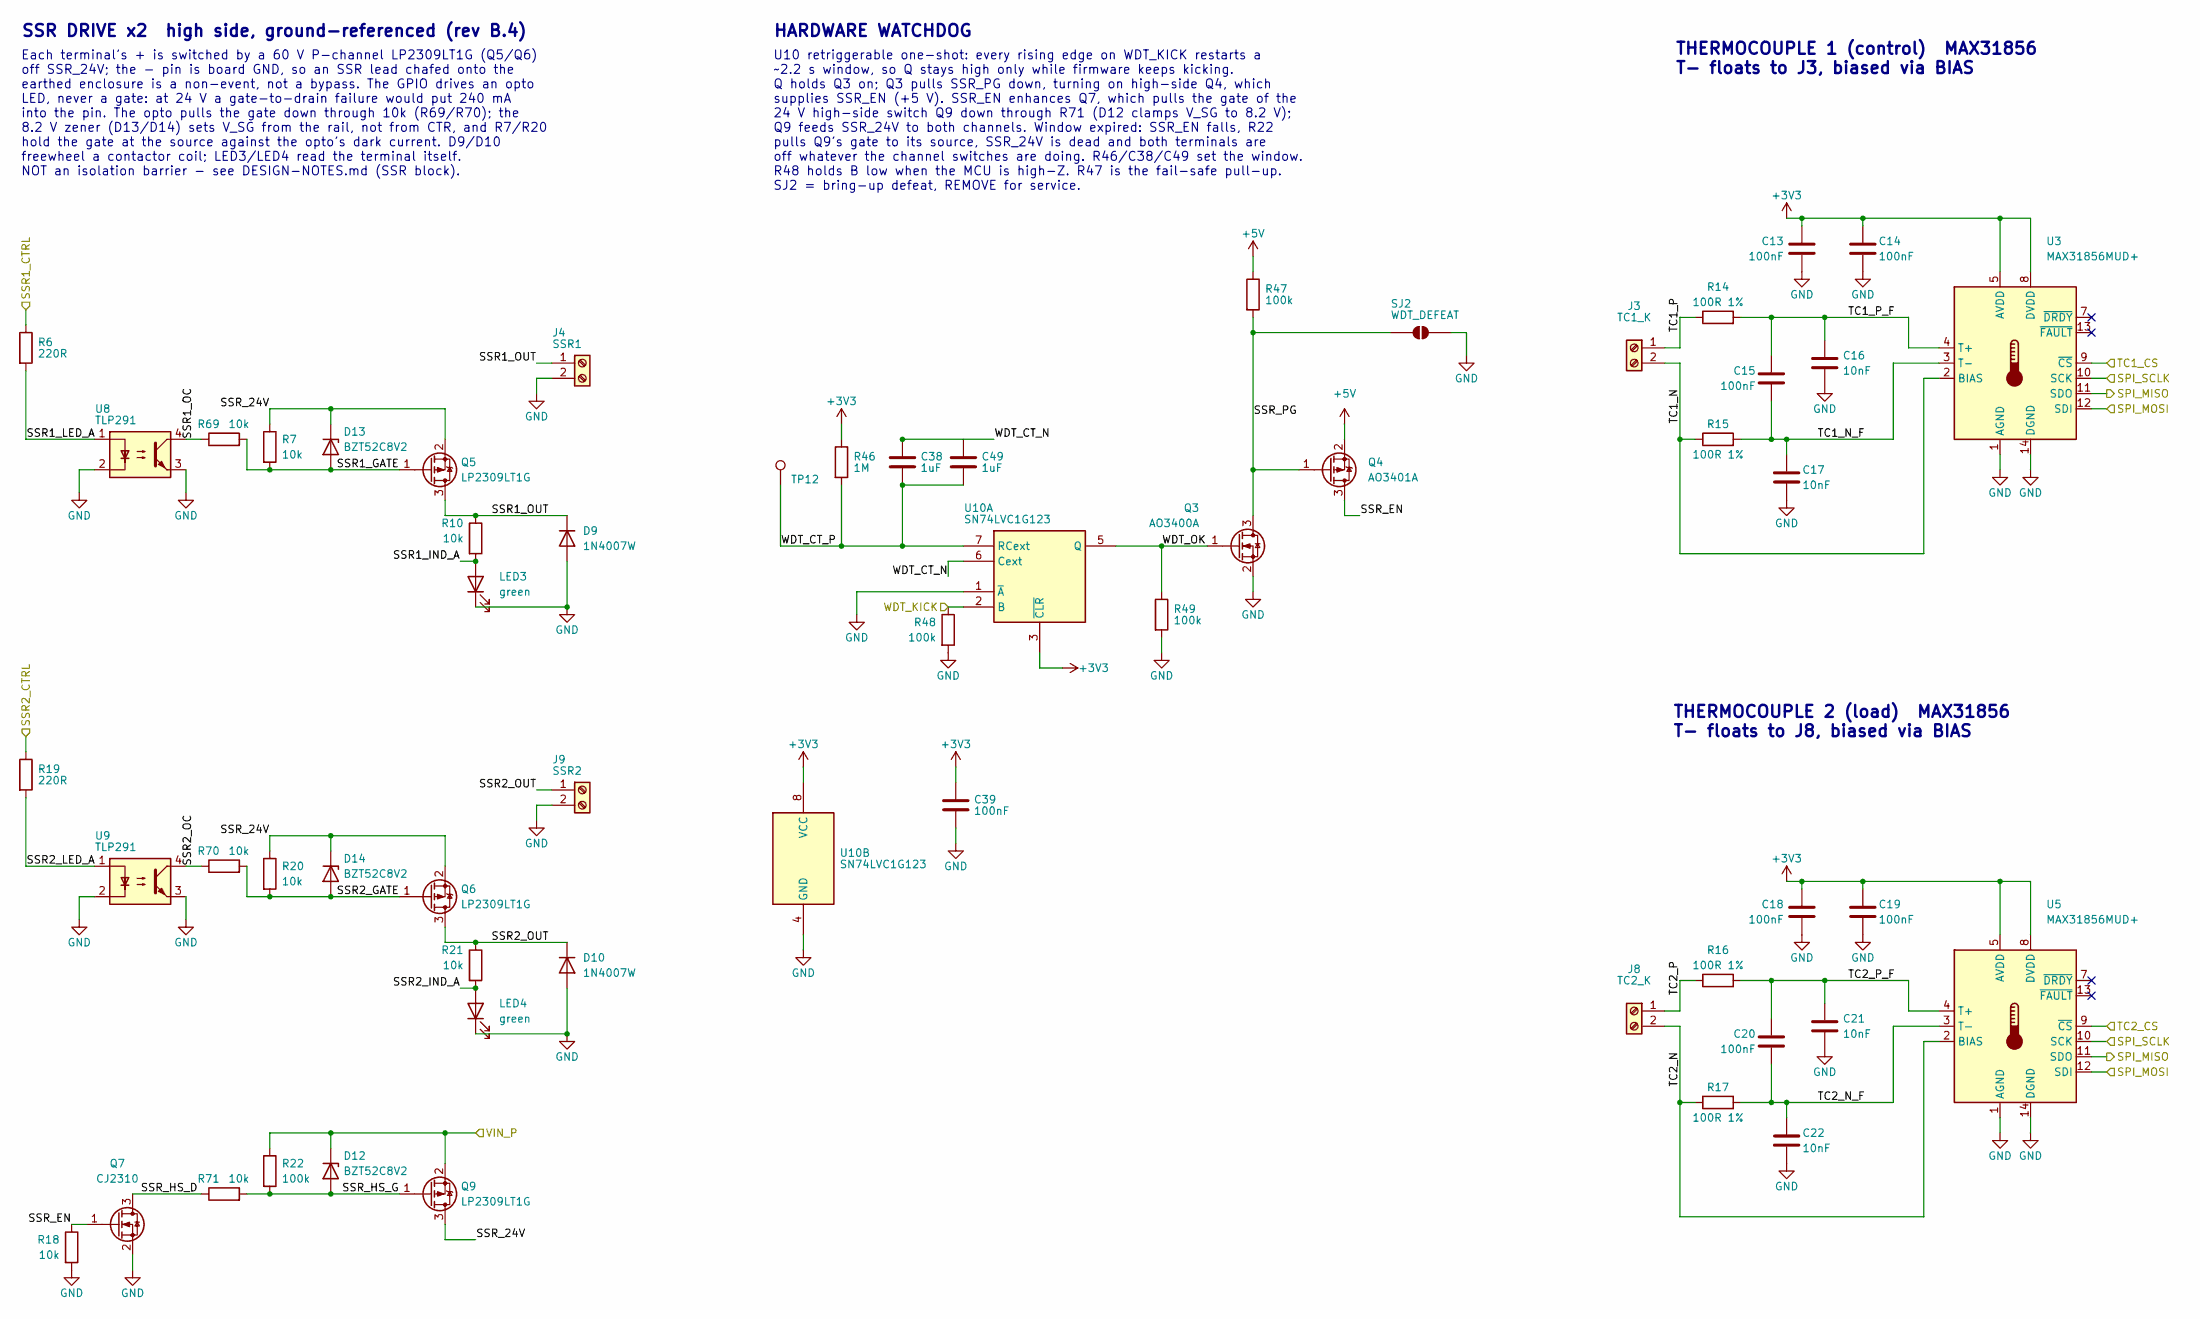
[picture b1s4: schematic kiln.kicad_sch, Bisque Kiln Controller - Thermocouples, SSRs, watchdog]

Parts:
C13, C14, C15, C18, C19, C20, C39: 100nF; C_0603_1608Metric; MPN CC0603KRX7R9BB104; LCSC C14663
C16, C17, C21, C22: 10nF; C_0805_2012Metric; MPN CL21B103KBANNNC; LCSC C1710
C38, C49: 1uF; C_0805_2012Metric; MPN CL21B105KBFNNNE; LCSC C28323
D9, D10: 1N4007W; D_SOD-123; MPN 1N4007W; LCSC C3018540
D12, D13, D14: BZT52C8V2; D_SOD-323; MPN BZT52C8V2S; LCSC C22375294
J3: TC1_K; TerminalBlock_Phoenix_MKDS-1,5-2-5.08_1x02_P5.08mm_Horizont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; MPN WJ500V-5.08-2P; LCSC C8465
J4: SSR1; TerminalBlock_Phoenix_MKDS-1,5-2-5.08_1x02_P5.08mm_Horizont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; MPN WJ500V-5.08-2P; LCSC C8465
J8: TC2_K; TerminalBlock_Phoenix_MKDS-1,5-2-5.08_1x02_P5.08mm_Horizont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; MPN WJ500V-5.08-2P; LCSC C8465
J9: SSR2; TerminalBlock_Phoenix_MKDS-1,5-2-5.08_1x02_P5.08mm_Horizont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; MPN WJ500V-5.08-2P; LCSC C8465
LED3, LED4: green; LED_0805_2012Metric; MPN KT-0805G; LCSC C2297
Q3: AO3400A; SOT-23; MPN AO3400A; LCSC C20917
Q4: AO3401A; SOT-23; MPN AO3401A; LCSC C15127
Q5, Q6, Q9: LP2309LT1G; SOT-23; MPN LP2309LT1G; LCSC C383253
Q7: CJ2310; SOT-23; MPN CJ2310; LCSC C75882
R6, R19: 220R; R_0805_2012Metric; MPN 0805W8F2200T5E; LCSC C17557
R7, R10, R18, R20, R21, R69, R70, R71: 10k; R_0805_2012Metric; MPN 0805W8F1002T5E; LCSC C17414
R14, R15, R16, R17: 100R 1%; R_0805_2012Metric; MPN 0805W8F1000T5E; LCSC C17408
R22, R47, R48, R49: 100k; R_0805_2012Metric; MPN 0805W8F1003T5E; LCSC C149504
R46: 1M; R_0805_2012Metric; MPN 0805W8F1004T5E; LCSC C17514
SJ2: WDT_DEFEAT; SolderJumper-2_P1.3mm_Open_RoundedPad1.0x1.5mm
TP12: WDT_CT_P; TestPoint_Pad_D1.0mm
U3, U5: MAX31856MUD+; TSSOP-14_4.4x5mm_P0.65mm; MPN MAX31856MUD+T; LCSC C2653162
U8, U9: TLP291; SOP-4_4.4x2.6mm_P1.27mm; MPN TLP291(GB-TP,SE; LCSC C55144
U10: SN74LVC1G123; SSOP-8_2.95x2.8mm_P0.65mm; MPN SN74LVC1G123DCTR; LCSC C123302

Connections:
+3V3: C13.1, C14.1, C18.1, C19.1, C39.1, R46.1, U3.5 (AVDD), U3.8 (DVDD), U5.5 (AVDD), U5.8 (DVDD), U10.3 (~CLR), U10.8 (VCC); also elsewhere on the board
+5V: Q4.2 (S), R47.1; also elsewhere on the board
GND: C13.2, C14.2, C16.2, C17.2, C18.2, C19.2, C21.2, C22.2, C39.2, D9.2 (A), D10.2 (A), J4.2, J9.2, LED3.1 (K), LED4.1 (K), Q3.2 (S), Q7.2 (S), R18.2, R48.2, R49.2, SJ2.2 (B), U3.1 (AGND), U3.14 (DGND), U5.1 (AGND), U5.14 (DGND), U8.2, U8.3, U9.2, U9.3, U10.1 (~A), U10.4 (GND); also elsewhere on the board
SPI_MISO: U3.11 (SDO), U5.11 (SDO); also elsewhere on the board
SPI_MOSI: U3.12 (SDI), U5.12 (SDI); also elsewhere on the board
SPI_SCLK: U3.10 (SCK), U5.10 (SCK); also elsewhere on the board
SSR1_CTRL: R6.1; also elsewhere on the board
SSR1_GATE: D13.2 (A), Q5.1 (G), R7.2, R69.2
SSR1_IND_A: LED3.2 (A), R10.2
SSR1_LED_A: R6.2, U8.1
SSR1_OC: R69.1, U8.4
SSR1_OUT: D9.1 (K), J4.1, Q5.3 (D), R10.1
SSR2_CTRL: R19.1; also elsewhere on the board
SSR2_GATE: D14.2 (A), Q6.1 (G), R20.2, R70.2
SSR2_IND_A: LED4.2 (A), R21.2
SSR2_LED_A: R19.2, U9.1
SSR2_OC: R70.1, U9.4
SSR2_OUT: D10.1 (K), J9.1, Q6.3 (D), R21.1
SSR_24V: D13.1 (K), D14.1 (K), Q5.2 (S), Q6.2 (S), Q9.3 (D), R7.1, R20.1
SSR_EN: Q4.3 (D), Q7.1 (G), R18.1
SSR_HS_D: Q7.3 (D), R71.1
SSR_HS_G: D12.2 (A), Q9.1 (G), R22.2, R71.2
SSR_PG: Q3.3 (D), Q4.1 (G), R47.2, SJ2.1 (A)
TC1_CS: U3.9 (~CS); also elsewhere on the board
TC1_N: J3.2, R15.1, U3.2 (BIAS)
TC1_N_F: C15.2, C17.1, R15.2, U3.3 (T-)
TC1_P: J3.1, R14.1
TC1_P_F: C15.1, C16.1, R14.2, U3.4 (T+)
TC2_CS: U5.9 (~CS); also elsewhere on the board
TC2_N: J8.2, R17.1, U5.2 (BIAS)
TC2_N_F: C20.2, C22.1, R17.2, U5.3 (T-)
TC2_P: J8.1, R16.1
TC2_P_F: C20.1, C21.1, R16.2, U5.4 (T+)
VIN_P: D12.1 (K), Q9.2 (S), R22.1; also elsewhere on the board
WDT_CT_N: C38.1, C49.1, U10.6 (Cext)
WDT_CT_P: C38.2, C49.2, R46.2, TP12.1, U10.7 (RCext)
WDT_KICK: R48.1, U10.2 (B); also elsewhere on the board
WDT_OK: Q3.1 (G), R49.1, U10.5 (Q)

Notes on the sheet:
SSR DRIVE x2 high side, ground-referenced (rev B.4)
Each terminal's + is switched by a 60 V P-channel LP2309LT1G (Q5/Q6) off SSR_24V; the - pin is board GND, so an SSR lead chafed onto the earthed enclosure is a non-event, not a bypass. The GPIO drives an opto LED, never a gate: at 24 V a gate-to-drain failure would put 240 mA into the pin. The opto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
HARDWARE WATCHDOG
U10 retriggerable one-shot: every rising edge on WDT_KICK restarts a ~2.2 s window, so Q stays high only while firmware keeps kicking. Q holds Q3 on; Q3 pulls SSR_PG down, turning on high-side Q4, which supplies SSR_EN (+5 V). SSR_EN enhances Q7, which pulls the gate of the 24 V high-side switch Q9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
THERMOCOUPLE 1 (control) MAX31856 T- floats to J3, biased via BIAS
THERMOCOUPLE 2 (load) MAX31856 T- floats to J8, biased via BIAS

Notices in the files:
hardware/kicad/README.md:
**Front:** `BISQUE / KILN CONTROLLER / REV C / © 2026 Ben Severson`, text
